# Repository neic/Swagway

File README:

The Swagway is a Segway clone.

It is a school project at HTX Frederikshavn.

It consists of a frame with two motors and gearbox assemblies from a powered wheelchair, a Arduino and some electronics.

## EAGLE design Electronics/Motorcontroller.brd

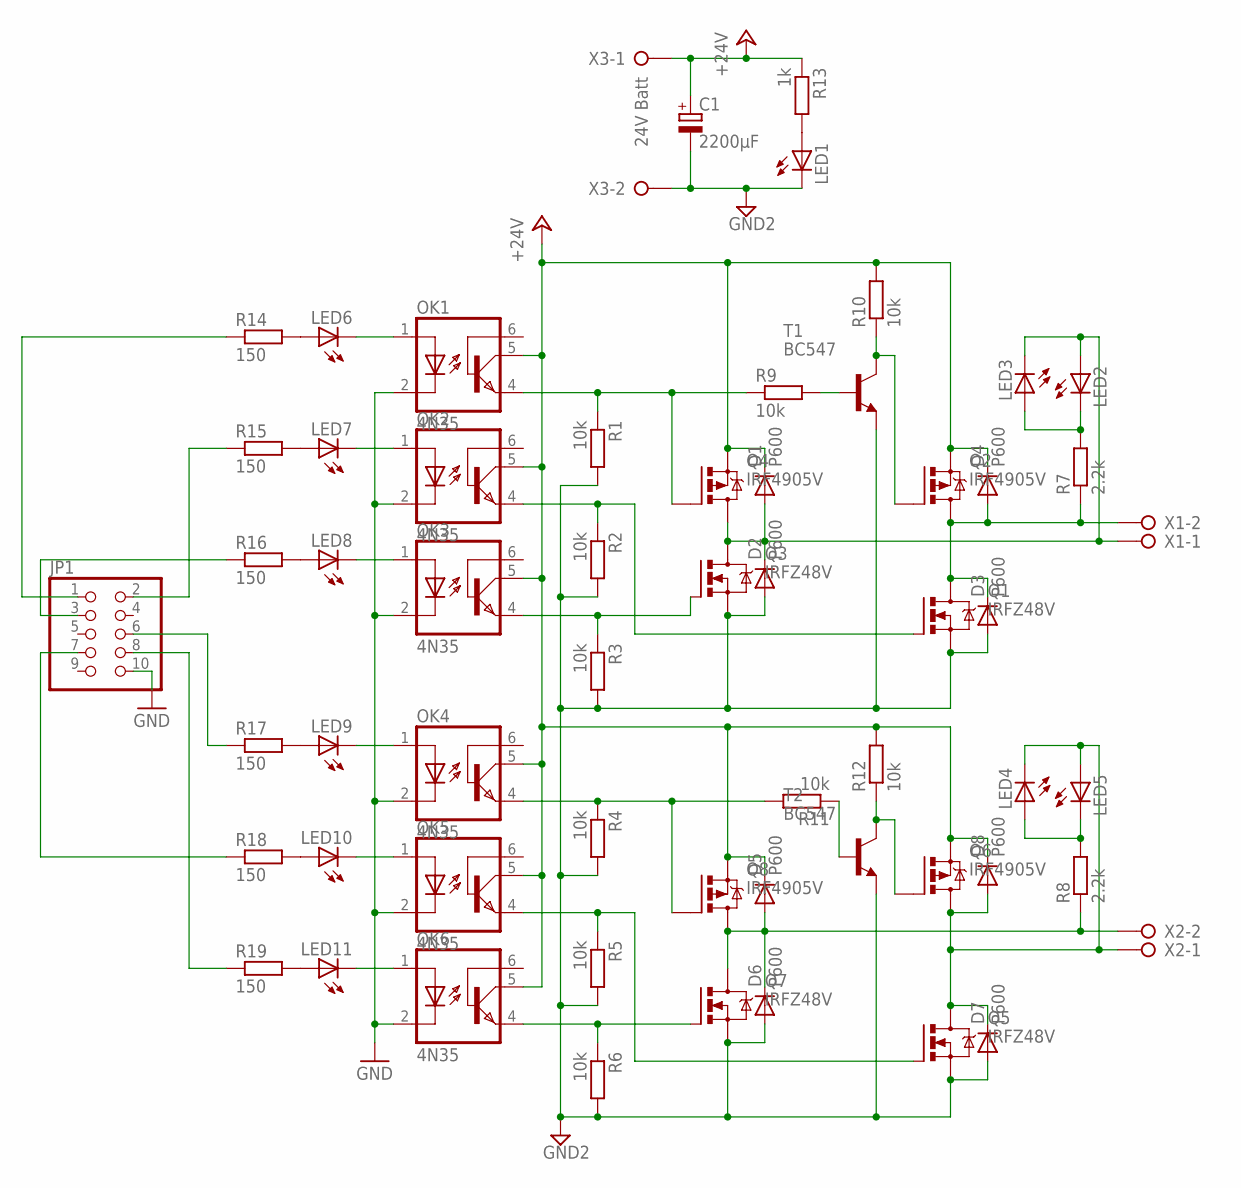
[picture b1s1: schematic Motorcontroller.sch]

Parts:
C1: 2200µF; E5-13
D1, D2, D3, D4, D5, D6, D7, D8: P600; P6-15
JP1: PINHD-2X5; 2X05
LED1, LED2, LED3, LED4, LED5, LED6, LED7, LED8, LED9, LED10, LED11: LED3MM
OK1, OK2, OK3, OK4, OK5, OK6: 4N35; DIL06
Q1, Q3, Q5, Q7: IRFZ48V; TO220BV
Q2, Q4, Q6, Q8: IRF4905V; TO220BV
R1, R2, R9, R10: 10k; 0207/7
R3, R4, R5, R6, R11, R12: 10k; 0207/10
R7, R8: 2.2k; 0207/2V
R13: 1k; 0207/2V
R14, R19: 150; 0207/7
R15, R16, R17, R18: 150; 0207/5V
T1, T2: BC547; TO92
X1, X2: W237-02P; W237-132
X3: 24V Batt; W237-132

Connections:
+24V: C1.+, D1.C, D4.C, D5.C, D8.C, OK1.5 (COL), OK2.5 (COL), OK3.5 (COL), OK4.5 (COL), OK5.5 (COL), OK6.5 (COL), Q2.S, Q4.S, Q6.S, Q8.S, R10.2, R12.2, R13.1, X3.1
GND: JP1.10, OK1.2 (C), OK2.2 (C), OK3.2 (C), OK4.2 (C), OK5.2 (C), OK6.2 (C)
GND2: C1.-, D2.A, D3.A, D6.A, D7.A, LED1.K (C), Q1.S, Q3.S, Q5.S, Q7.S, R1.2, R2.2, R3.2, R4.2, R5.2, R6.2, T1.1 (E), T2.1 (E), X3.2
unnamed: D7.C, D8.A, LED4.K (C), LED5.A, Q5.D, Q6.D, X2.1
unnamed: JP1.1, R14.1
unnamed: D3.C, D4.A, Q1.D, Q2.D, R7.1, X1.2
unnamed: JP1.2, R15.1
unnamed: LED1.A, R13.2
unnamed: JP1.3, R16.1
unnamed: JP1.6, R17.1
unnamed: OK2.4 (EMI), Q1.G, R2.1
unnamed: JP1.7, R18.1
unnamed: JP1.8, R19.1
unnamed: OK1.4 (EMI), Q4.G, R1.1, R9.1
unnamed: OK3.4 (EMI), Q3.G, R3.1
unnamed: R9.2, T1.2 (B)
unnamed: Q2.G, R10.1, T1.3 (C)
unnamed: OK4.4 (EMI), Q8.G, R4.1, R11.2
unnamed: LED10.A, R18.2
unnamed: R11.1, T2.2 (B)
unnamed: Q6.G, R12.1, T2.3 (C)
unnamed: LED6.A, R14.2
unnamed: OK5.4 (EMI), Q5.G, R5.1
unnamed: OK6.4 (EMI), Q7.G, R6.1
unnamed: LED2.K (C), LED3.A, R7.2
unnamed: LED4.A, LED5.K (C), R8.2
unnamed: LED7.A, R15.2
unnamed: LED8.A, R16.2
unnamed: LED9.A, R17.2
unnamed: LED11.A, R19.2
unnamed: LED6.K (C), OK1.1 (A)
unnamed: LED7.K (C), OK2.1 (A)
unnamed: LED8.K (C), OK3.1 (A)
unnamed: LED9.K (C), OK4.1 (A)
unnamed: LED10.K (C), OK5.1 (A)
unnamed: LED11.K (C), OK6.1 (A)
unnamed: D1.A, D2.C, LED2.A, LED3.K (C), Q3.D, Q4.D, X1.1
unnamed: D5.A, D6.C, Q7.D, Q8.D, R8.1, X2.2

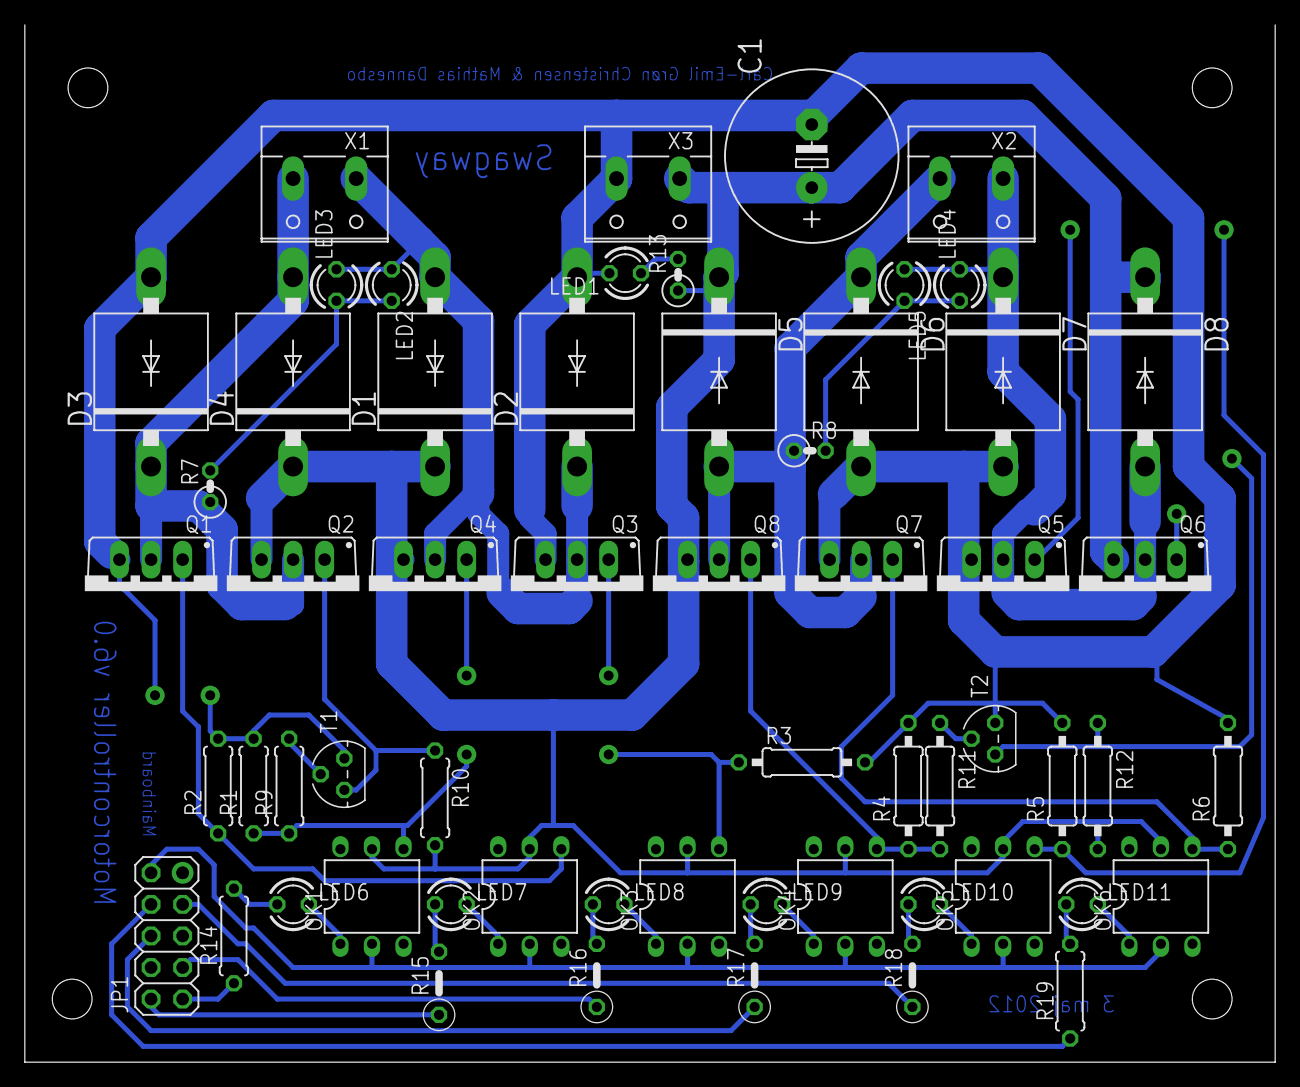
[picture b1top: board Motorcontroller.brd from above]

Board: 2 copper layers, 100.6 x 83.5 mm, 59 parts (0 on the bottom side), 38 nets.

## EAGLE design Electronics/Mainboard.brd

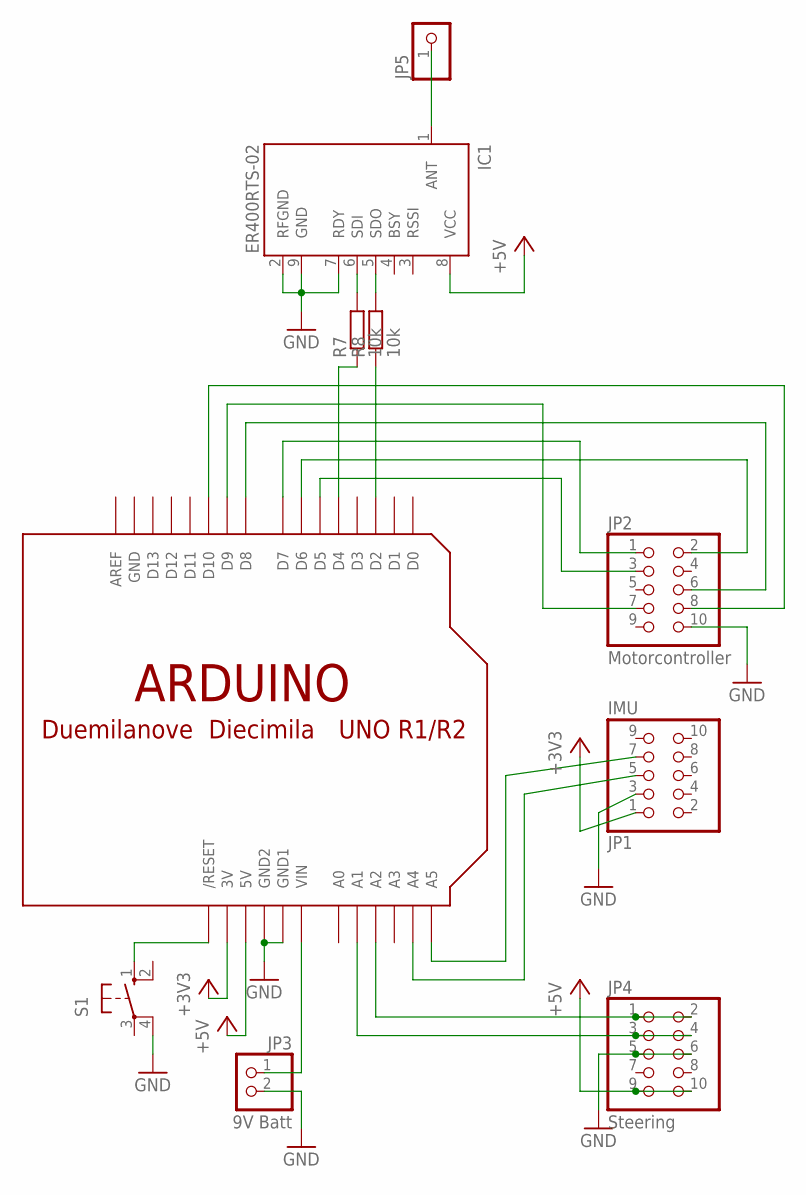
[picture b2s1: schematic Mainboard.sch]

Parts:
IC1: ER400RTS-02; SIL9
JP1: IMU; 2X05
JP2: Motorcontroller; 2X05
JP3: 9V Batt; 1X02
JP4: Steering; 2X05
JP5: PINHD-1X1; 1X01
R7, R8: 10k; 0207/10
S1: 10-XX; B3F-10XX
U$1: ARDUINOUNO; ARDUINO

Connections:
+3V3: JP1.1, U$1.3V
+5V: IC1.8 (VCC), JP4.9, JP4.10, U$1.5V
GND: IC1.2 (RFGND), IC1.7 (RDY), IC1.9 (GND), JP1.3, JP2.10, JP3.2, JP4.5, JP4.6, S1.4 (P1), U$1.GND, U$1.GND1, U$1.GND2
unnamed: JP2.1, U$1.D7
unnamed: JP2.2, U$1.D6
unnamed: JP2.6, U$1.D8
unnamed: JP2.8, U$1.D10
unnamed: JP2.3, U$1.D5
unnamed: R8.1, U$1.D2
unnamed: R7.1, U$1.D4
unnamed: JP4.3, JP4.4, U$1.A1
unnamed: JP4.1, JP4.2, U$1.A2
unnamed: S1.1 (S), U$1.RESET (/RESET)
unnamed: JP2.7, U$1.D9
unnamed: IC1.5 (SDO), R8.2
unnamed: IC1.6 (SDI), R7.2
unnamed: IC1.1 (ANT), JP5.1
unnamed: JP1.7, U$1.A5
unnamed: JP3.1, U$1.VIN
unnamed: JP1.5, U$1.A4

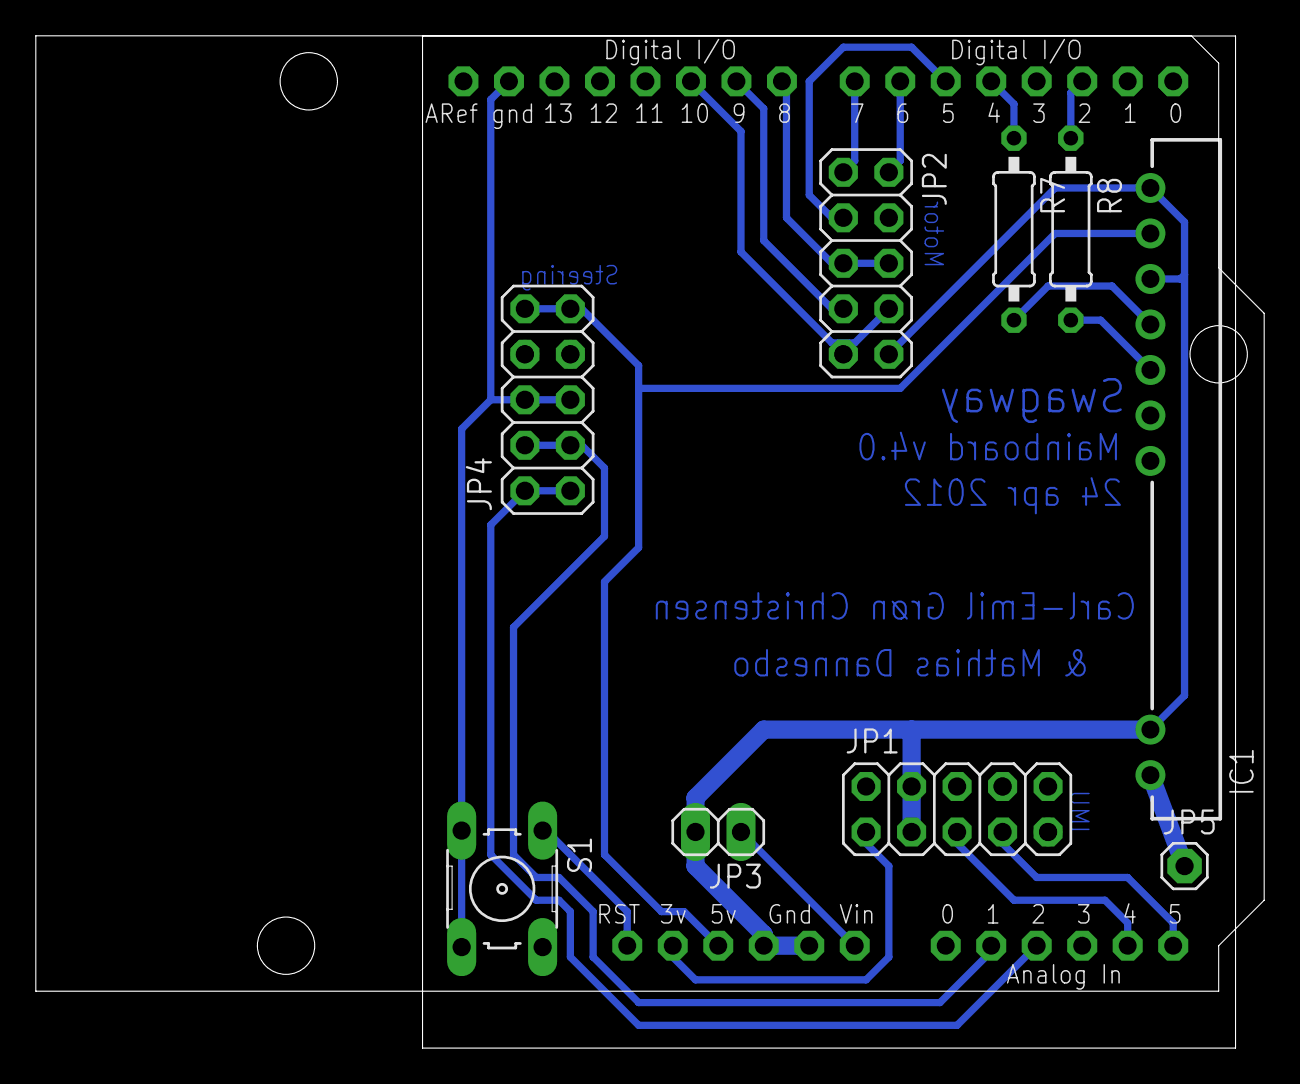
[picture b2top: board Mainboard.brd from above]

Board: 2 copper layers, 68.6 x 56.5 mm, 10 parts (0 on the bottom side), 20 nets.

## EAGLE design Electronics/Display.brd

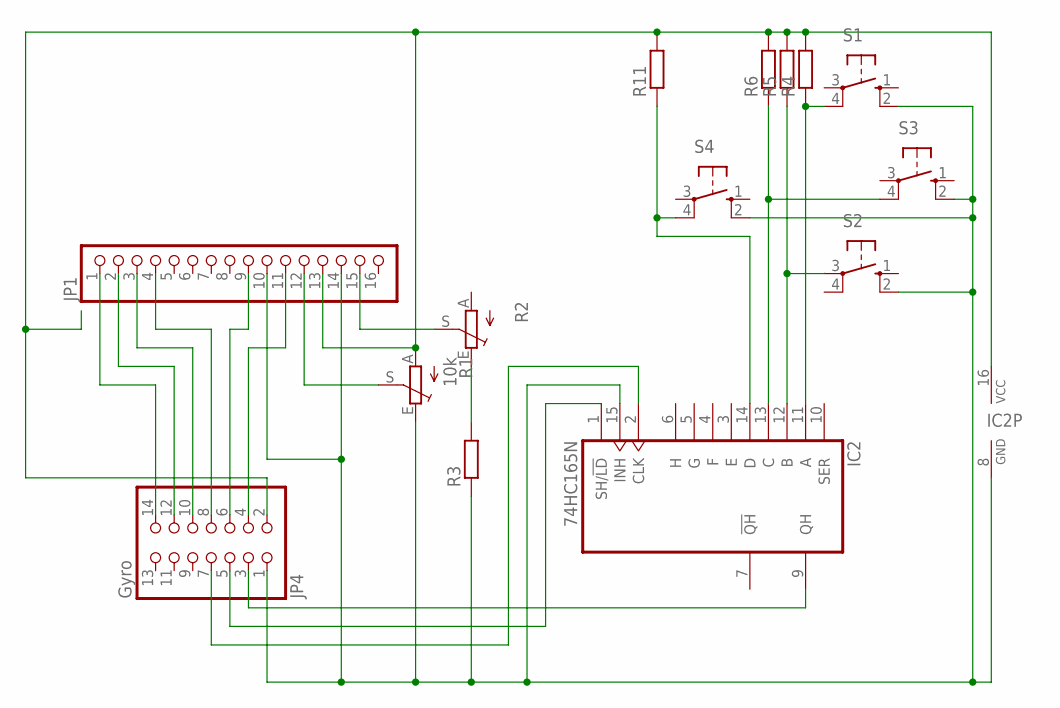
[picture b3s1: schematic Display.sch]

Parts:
IC2: 74HC165N; DIL16
JP1: PINHD-1X16; 1X16
JP4: Gyro; 2X07
R1: 10k; CA9H
R2: TRIM_EU-CA9H; CA9H
R3, R4, R5, R6, R11: R-EU_0207/10; 0207/10
S1, S2, S3, S4: 10-XX; B3F-10XX

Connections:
unnamed: JP1.15, R2.S
unnamed: IC2.8 (GND), IC2.15 (INH), JP1.10, JP1.14, JP4.1, R1.E, R3.1, S1.2 (S1), S2.2 (S1), S3.2 (S1), S4.2 (S1)
unnamed: JP1.13, JP4.2, R1.A, R4.2, R5.2, R6.2, R11.2
unnamed: R2.E, R3.2
unnamed: JP1.11, JP4.4
unnamed: IC2.1 (SH/!LD), JP4.5
unnamed: JP1.12, R1.S
unnamed: IC2.9 (QH), JP4.3
unnamed: IC2.2 (CLK), JP4.7
unnamed: JP1.9, JP4.6
unnamed: JP1.4, JP4.8
unnamed: JP1.3, JP4.10
unnamed: JP1.2, JP4.12
unnamed: JP1.1, JP4.14
unnamed: IC2.11 (A), R4.1, S1.4 (P1)
unnamed: IC2.12 (B), R5.1, S2.3
unnamed: IC2.13 (C), R6.1, S3.4 (P1)
unnamed: IC2.14 (D), R11.1, S4.4 (P1)
VCC: IC2.16 (VCC)

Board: 2 copper layers, 14 parts (0 on the bottom side), 18 nets, no tracks yet.

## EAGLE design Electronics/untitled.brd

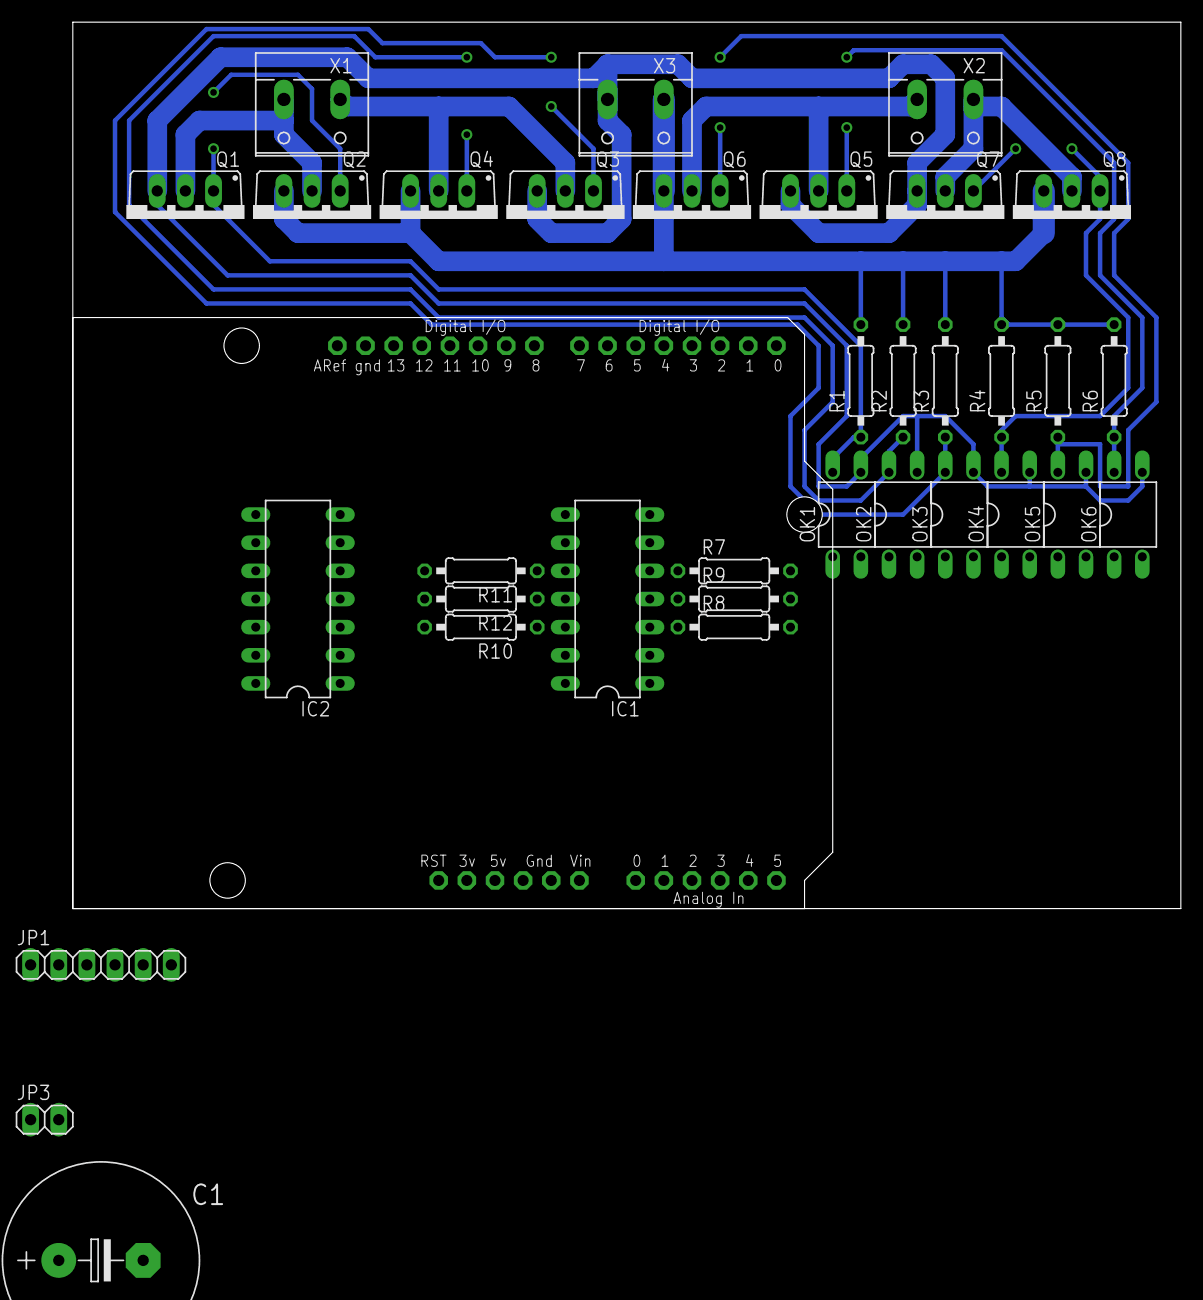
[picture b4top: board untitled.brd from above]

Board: 2 copper layers, 100.0 x 80.0 mm, 35 parts (0 on the bottom side), 34 nets.

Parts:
C1: E7,5-18
IC1: 4081N; DIL14
IC2: 4069N; DIL14
JP1: Gyro; 1X06
JP3: 9V Batt; 1X02
OK1, OK2, OK3, OK4, OK5, OK6: PC817; DIL04
Q1, Q3, Q5, Q7: IRFZ48V; TO220BV
Q2, Q4, Q6, Q8: IRF4905V; TO220BV
R1, R2, R3, R4, R5, R6: 10k; 0207/10
R7, R8, R9, R10, R11, R12: 0207/10
U$1: ARDUINOUNO; ARDUINO
X1, X2: W237-132
X3: 24V Batt; W237-132

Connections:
GND: IC1.7, IC2.7, JP1.2, JP3.2, OK1.2, OK2.2, OK3.2, OK4.2, OK5.2, OK6.2, U$1.GND, U$1.GND1, U$1.GND2
unnamed: Q5.D, Q6.D, X2.2
unnamed: Q3.D, Q4.D, X1.1
unnamed: OK2.1, R8.2
unnamed: Q1.D, Q2.D, X1.2
unnamed: OK4.1, R10.2
unnamed: IC1.9, IC1.13, U$1.D5
unnamed: IC1.1, IC2.2
unnamed: OK2.4, Q4.G, R2.1
unnamed: IC1.5, IC2.1, R7.1, U$1.D2
unnamed: IC1.2, IC1.6, U$1.D3
unnamed: OK1.4, Q1.G, Q2.G, R1.1
unnamed: OK3.4, Q3.G, R3.1
unnamed: OK3.1, R9.2
unnamed: IC1.3, R8.1
unnamed: IC1.8, IC2.4
unnamed: IC1.4, R9.1
unnamed: Q7.D, Q8.D, X2.1
unnamed: OK4.4, Q7.G, Q8.G, R4.1
unnamed: OK5.1, R11.2
unnamed: OK5.4, Q6.G, R5.1
unnamed: OK6.4, Q5.G, R6.1
unnamed: OK6.1, R12.2
unnamed: IC1.10, R11.1
unnamed: IC1.11, R12.1
unnamed: JP1.4, U$1.A5
unnamed: IC1.12, IC2.3, R10.1, U$1.D4
unnamed: OK1.1, R7.2
unnamed: C1.-, OK1.3, OK2.3, OK3.3, OK4.3, OK5.3, OK6.3, Q1.S, Q3.S, Q5.S, Q7.S, X3.2
unnamed: C1.+, Q2.S, Q4.S, Q6.S, Q8.S, R1.2, R2.2, R3.2, R4.2, R5.2, R6.2, X3.1
unnamed: JP1.1, U$1.3V
unnamed: JP1.3, U$1.A4
unnamed: JP3.1, U$1.VIN
VCC: IC1.14, IC2.14, U$1.5V

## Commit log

2012-01-15 second commit
2012-01-15 Added Electronics
2012-01-15 Basic info
2012-01-15 Typos
2012-01-15 Deleted garbage
2012-01-18 Arduino sofware, updated electronics and some report outline.
2012-01-19 Deleted out-commented code
2012-01-25 Typo
2012-01-25 Split board
2012-01-25 Besked
2012-01-25 Code tidy-up
2012-01-25 Added gyro calibration. Closes #6.
2012-01-27 Debug graph app draft in processing.
2012-01-27 Updated graph
2012-01-27 Many improvements to graph
2012-02-08 Non-working kalman-filter
2012-02-08 Removing emacs garbage
2012-02-10 Working non-tuned Kalman filter
2012-03-01 Mainboard 2.0. Fixes #1, #2 #12
2012-03-06 Kalman trial and error
2012-03-06 Small outline addition
2012-03-06 Added projektoplæg
2012-03-07 Motorboard v2.0
2012-03-08 Motorboard: pad sizes and small reroutes
2012-03-08 Few proximity reroutes
2012-03-08 Updated pdf
2012-03-09 Updated .sch to be consisting to .brd (it was missing from the last commit)
2012-03-09 Reroute around header
2012-03-09 Bumped version number and updated pdf
2012-03-12 Moved graph to Software/graph
2012-03-12 Added temp files to a .gitignore
2012-03-12 Cleanup of readme
2012-03-13 Added build log
2012-03-15 Motor control scheme
2012-03-15 New motorboard test
2012-03-16 Trying to debug the gyro angle
2012-03-16 Updated .gitignore
2012-03-17 Better structured test
2012-03-17 Test with PWM
2012-03-17 New Kalman-filter and some tidy-up
2012-03-17 Proper mapping
2012-03-17 Outline for new graph software in C#
2012-03-17 Deleted temp- and settings-files
2012-03-17 Ignored temp- and settings-files
2012-03-17 Serial port: connecting and receiving
2012-03-17 More robust serial port
2012-03-17 Even more robust serial
2012-03-18 Sending serial data
2012-03-21 Data cleaning and samples/sec
2012-03-26 Renamed HEXFETs so both bridge fit
2012-03-26 Wrote the motor control scheme so it actually fits the electronics
2012-03-26 Renamed the second bridge HEXFETs
2012-03-26 New mainboard. Closes #13, closes #21 and closes #9 as it becomes irrelevant.
2012-03-26 Table with pin connections and updated motor control scheme
2012-03-29 Redesign of motorboard. Closes #30
2012-03-29 Updated .pdf
2012-03-29 Radio on mainboard. Closes #29
2012-04-03 First test with gyro lib
2012-04-03 Reciving the right data from the gyro with the gyrolib. Closes #20
2012-04-03 More robust gyroSampleRate
2012-04-03 Nicer dumpIMUsettings and typo
2012-04-03 Removed a lot of old code
2012-04-03 Framework for acc lib
2012-04-03 Most setup functions complete
2012-04-03 Rewrote to work with the new acc lib
2012-04-04 added acc.setOutputRate()
2012-04-04 added acc.isRawDataReady()
2012-04-04 added acc.readAccRaw()
2012-04-04 Added acc.readAcc() and a dumb acc.setScaleFactor()
2012-04-04 Added FullRes functions
2012-04-04 Added acc.range functions and updated dumpIMUsettings()
2012-04-04 Smarter scalefactor
2012-04-04 Tidy up
2012-04-04 Parsed the news data from the gyro and acc to the Kalman-filter, better names and some clean-up.
2012-04-05 Brackets around serial package
2012-04-06 More robust dataClean(). Closes #22
2012-04-06 Rolling Graph. Closes #24
2012-04-12 New motorcontroller with pull-down
2012-04-13 Reroute and tidy-up. New version number
2012-04-13 New .pdf
2012-04-13 Updated motor control scheme to fit with the new motorboard
2012-04-13 Description of Motorcontroller versions
2012-04-17 Fixed airwire in motorboard. Updated .pdf and rapport
2012-04-17 New Motorboard_test for the new motorcontroller
2012-04-20 First connection between IMU and motor
2012-04-24 Moved resistors to Motorboard. Closes #37
2012-04-24 Updated .pdfs
2012-04-24 Added LEDs to optocoupelers. Closes #39
2012-04-24 Changed pins on pinheader
2012-04-24 Route of small airwire
2012-04-24 Updated Motorcontroller and Mainboard changelog
2012-04-26 Test motorcontrol with static speed
2012-04-27 Proportional motorcontrol
2012-04-27 Changed pin 5 and 9. Closes #42
2012-04-30 Added PID. Closes #3
2012-05-01 New type of PID
2012-05-02 Multiple Kp & Ti
2012-05-03 Motorcontroller with protection diodes. Also closes #40
2012-05-06 Updated rapport
2012-05-06 Rapport: new outline
2012-05-07 exponential function
2012-05-07 added sources
2012-05-07 Added header
2012-05-07 testing
2012-05-07 Added source code
2012-05-07 Reset to motorcontroller v5.2
2012-05-07 Added thanks
2012-05-07 Ignored unsorted pictures
2012-05-07 Added Motorcontroller v5.2 sch
2012-05-07 Added Motorcontroller v2.1 sch
2012-05-08 Changed I2C section
2012-05-08 PWM text and figure
2012-05-08 Ignored temp bibtex files
2012-05-08 Init the bibliography
2012-05-08 rewrote I2C section
2012-05-08 Indledning
2012-05-08 Edited small stuff in I2C, added gyro subsubsection
2012-05-09 Removed the PID tap. Closes #26 and closes #27
2012-05-09 Commented code
2012-05-09 Removed autoscroll checkbox (closes #23) and polar plot (closes #25)
2012-05-09 Added functionality behind threshold selector
2012-05-09 Garbage collection of monitor. Closes #36
2012-05-09 Init Debug rapport
2012-05-09 Debug software tester
2012-05-09 Icon, index bug and monitor size
2012-05-09 Fixed whitespace, indentation and some typos
2012-05-09 Indledning and first part of Instillinger
2012-05-10 Last part of Indstillinger and first part og Seriel modtagelse og monitor
2012-05-10 Last parts of Debug rapport
2012-05-10 Small changes and typos
2012-05-10 Screenshots
2012-05-10 Screenshots crop
2012-05-10 Added screenshots and abstract
2012-05-10 Final touch-up
2012-05-10 rewrote, fixed typos and added small stuff several places
2012-05-10 Rewrote several parses of boards
2012-05-10 Rewrote motorboard section
2012-05-10 Gyro and acc theory and frontpage
2012-05-10 Rewrote motorboard issues
2012-05-10 typos everywhere
2012-05-10 Rewrote introduction
2012-05-10 Inproved frontmatter
2012-05-10 society value of motion sensoring
2012-05-10 Added Accelerometer info
2012-05-10 Added basic I2C figure
2012-05-10 Added accbasic figure
2012-05-10 Typos and outline
2012-05-10 Added subsections for steering part
2012-05-10 Added steering section
2012-05-10 Rewrote xboard section
2012-05-10 Small changes to I2C
2012-05-11 Added I2C read and write
2012-05-11 Wrote H-bridge theory
2012-05-11 clean-up and IMU biblioter init. atmega in bib
2012-05-11 Added text on filters
2012-05-11 IMU biblioteker
2012-05-11 whitespace
2012-05-11 updated notes and outline
2012-05-11 Wrote Regulations
2012-05-11 More IMU bibliotek
2012-05-11 Typo and updated .pdf
2012-05-11 Last part of IMU lib
2012-05-11 Added picture
2012-05-11 Added refence. Removed small errors
2012-05-11 Added H-brigde picture
2012-05-11 Moved boarddate to margin
2012-05-11 Text size and small inprovements
2012-05-11 Picture of fried motorcontroller
2012-05-11 added pictures of old motorboards
2012-05-11 Added main loop section
2012-05-11 lot of small improvements
2012-05-11 removed fixme
2012-05-11 added No-cheat promise
2012-05-11 Added PID figure
2012-05-11 Added TroogLove.pdf
2012-05-11 final touch
2012-05-11 removed fixmes, added arbejdsdeling
2012-05-11 final touch up
